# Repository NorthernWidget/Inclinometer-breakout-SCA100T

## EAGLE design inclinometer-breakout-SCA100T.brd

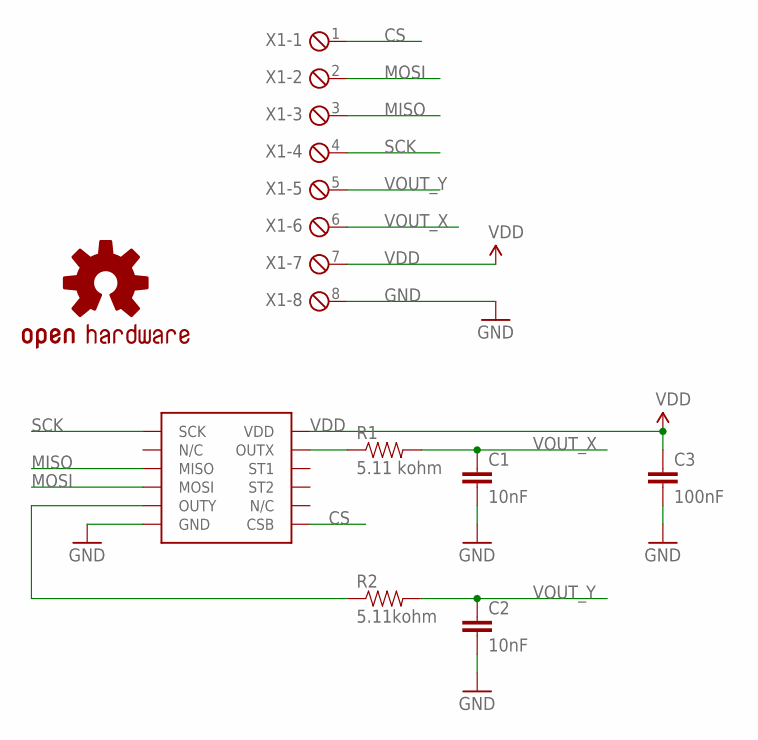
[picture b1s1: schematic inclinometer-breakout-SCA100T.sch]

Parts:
C1, C2: 10nF; 0603-CAP
C3: 100nF; 0603-CAP
LOGO1: OSHW-LOGOM; OSHW-LOGO-M
R1: 5.11 kohm; 0603-RES
R2: 5.11kohm; 0603-RES
U$1: SCA100T; SCA1000
X1: MPT8; 8POL254

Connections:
CS: U$1.7 (CSB), X1.1
GND: C1.2, C2.2, C3.2, U$1.6 (GND), X1.8
MISO: U$1.3 (MISO), X1.3
MOSI: U$1.4 (MOSI), X1.2
unnamed: R1.1, U$1.11 (OUTX)
unnamed: R2.1, U$1.5 (OUTY)
SCK: U$1.1 (SCK), X1.4
VDD: C3.1, U$1.12 (VDD), X1.7
VOUT_X: C1.1, R1.2, X1.6
VOUT_Y: C2.1, R2.2, X1.5

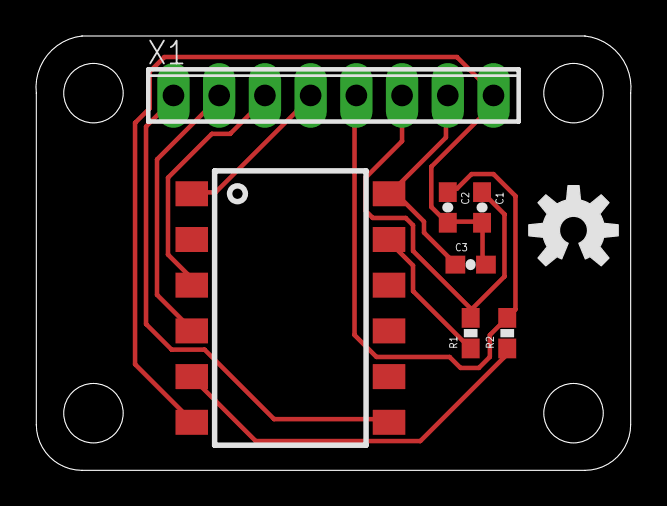
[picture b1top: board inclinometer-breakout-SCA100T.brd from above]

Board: 2 copper layers, 33.1 x 24.1 mm, 12 parts (0 on the bottom side), 10 nets.

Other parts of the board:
JP1, JP2, JP3, JP4: STAND-OFF

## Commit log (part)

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2016-04-27 Schematic has all components
2016-04-27 datasheet
2016-04-27 CC-BY-SA
2017-04-11 updated files

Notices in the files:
parts and their libraries:
SparkFun-Sensors: Licensing: Creative Commons ShareAlike 4.0 International - https://creativecommons.org/licenses/by-sa/4.0
